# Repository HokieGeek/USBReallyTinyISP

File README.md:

# USBReallyTinyISP
SMT version of [Adafruit's USBtinyISP](https://learn.adafruit.com/usbtinyisp) with a form factor inspired by [SparkFun's AVR Adapter](http://www.sparkfun.com/products/retired/8508).

 This work is licensed as  *Creative Common 4.0 Attribution-ShareAlike*
## Schematic

## Board

## Datasheets
* [ATtiny2313](http://www.atmel.com/images/doc2543.pdf)
* [74AHC125](http://www.ti.com/lit/ds/symlink/sn74ahc125.pdf)

[Mouser project](https://www.mouser.com/ProjectManager/ProjectDetail.aspx?ProjectGUID=dc6b4dca-204f-45ba-9732-e10048a6dd5b)

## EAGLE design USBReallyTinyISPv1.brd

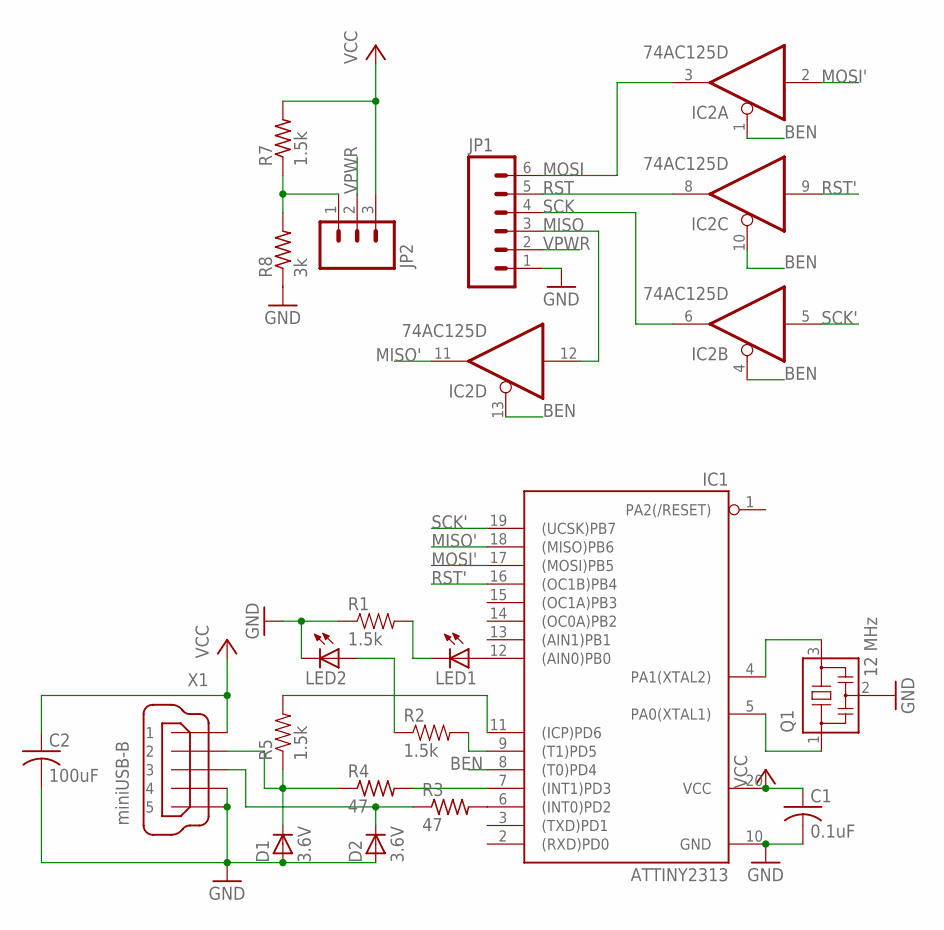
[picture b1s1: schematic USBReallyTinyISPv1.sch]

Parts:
C1: 0.1uF; C0805
C2: 100uF; C1206
D1, D2: 3.6V; SOD3718X135N
IC1: ATTINY2313; SO20L$
IC2: 74AC125D; SO14
JP1: M06SILK_FEMALE_PTH; 1X06
JP2: M03-SHORTEDPTH; 1X03
LED1, LED2: LEDSML0805; SML0805
Q1: 12 MHz; CSTCR6M
R1, R2, R5: 1.5k; 1206
R3, R4: 47; R0805
R7: 1.5k; R0805
R8: 3k; R0805
X1: miniUSB-B; UX60A-MB-5ST

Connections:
BEN: IC1.8 ((T0)PD4), IC2.1 (OE), IC2.4 (OE), IC2.10 (OE), IC2.13 (OE)
GND: C1.2, C2.2, D1.A, D2.A, IC1.10 (GND), IC2.7 (GND), JP1.1, LED2.C, Q1.2, R1.1, R8.1, X1.4, X1.5
MISO: IC2.12 (I), JP1.3
MISO': IC1.18 ((MISO)PB6), IC2.11 (O)
MOSI: IC2.3 (O), JP1.6
MOSI': IC1.17 ((MOSI)PB5), IC2.2 (I)
unnamed: IC1.12 ((AIN0)PB0), LED1.A
unnamed: IC1.4 (PA1(XTAL2)), Q1.3
unnamed: IC1.5 (PA0(XTAL1)), Q1.1
unnamed: IC1.9 ((T1)PD5), R2.2
unnamed: LED2.A, R2.1
unnamed: LED1.C, R1.2
unnamed: IC1.6 ((INT0)PD2), R3.2
unnamed: IC1.7 ((INT1)PD3), R4.2
unnamed: D2.K, R3.1, X1.3
unnamed: D1.K, R4.1, R5.1, X1.2
unnamed: IC1.11 ((ICP)PD6), R5.2
unnamed: JP2.1, R7.1, R8.2
RST: IC2.8 (O), JP1.5
RST': IC1.16 ((OC1B)PB4), IC2.9 (I)
SCK: IC2.6 (O), JP1.4
SCK': IC1.19 ((UCSK)PB7), IC2.5 (I)
VCC: C1.1, C2.1, IC1.20 (VCC), IC2.14 (VCC), JP2.3, R7.2, X1.1
VPWR: JP1.2, JP2.2

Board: 2 copper layers, 19 parts (13 on the bottom side), 24 nets, no tracks yet.

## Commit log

2015-10-09 Creating a README
2015-10-13 Getting it ready for printing
2015-10-13 Adding a pic of the schematic
2015-10-13 Does not really matter
2015-10-14 Really rethought the board arrangement and rerouted
2015-10-14 Added schematic to the readme
2015-10-14 Added board image
2015-10-27 Got my boards back from OSH Park and really need bigger text!
2015-10-27 Totally got the year wrong on the board.
2015-10-27 Because it was just too big
2015-10-28 Lots of tweaks to get a tiny little board!
2015-10-28 Tweak Tweak!
2015-10-30 Changed size of 1.5kOhm resistors
2015-10-30 Updated headers to have bigger pads
2015-10-31 Rerouted based on some updates
2015-11-02 Working on the schematic as I start to find flaws in my design
2015-11-11 Finally removed that freaking border

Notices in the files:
README.md:
CC BY-SA 3.0
parts and their libraries:
SparkFun-Resistors: Licensing: Creative Commons ShareAlike 4.0 International - https://creativecommons.org/licenses/by-sa/4.0
